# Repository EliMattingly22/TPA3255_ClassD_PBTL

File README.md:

# TPA3255_ClassD_PBTL
A KiCAD project for the TPA3255 amplifier in PBTL mode

This repository contains schematics, PCB layout and documentation for a compact, rack mountable PBTL (Parallel Bridged) Class‑D amplifier based on the Texas Instruments TPA3255. The design is intended to house three amplifier modules in a single 2U rack enclosure and includes front‑panel controls such as button‑enabled DC‑coupling, balanced XLR inputs/outputs, and protection/status indicators.

## Features

- TPA3255 Class‑D amplifier modules configured in PBTL(parallel bridge-tied load) mode
- Per‑channel button to toggle DC‑coupling
- Balanced XLR inputs
- Per‑channel protection: overcurrent, overtemperature, 
- Clipping indicators
- Per‑channel status LEDs (PWR GOOD / CLIP / FAULT)
- Mechanical layout and enclosure guidance for three amplifiers in a 2U rack unit

## Key electrical parameters

- Supply voltage - 24-52V
  - Power supply current rating should be sufficient for your load. At 50V a 12A supply will be enough for any application, but less is suitable for many other applications. 
- Gain is fixed. G = 21.6(2 Ohms) to 24.4(15 Ohms)
- THD depends on amplitude/power but generally 0.1-0.5%. Better than that in some operating conditions/power levels. 
- Output noise (1-25kHz) is approximately 2 microVolts/sqrt(Hz) 
- Quiescent power draw - about 100 mA per channel

## Overview

This project is intended as a general-purpose amplifier capable of replacing the AE Techron 7224 in a variety of lower-power applications. It is a high‑efficiency, medium‑power (300 Watt for sure and up to 600W, in theory...) amplifier solution with balanced I/O and configurable output coupling. The DC‑coupling button lets users switch the amplifier output between AC coupling and DC coupling for use with audio systems or laboratory instruments, etc. that require true DC‑coupled operation. The enclosure is designed to hold three amplifier modules in a 19" 2U rack, with appropriate heatsinking and airflow considerations.

### In this repository:

 - The enclosure is in the top level as: "TPA3255PBTL_Enclosure.step" [Here](TPA3255PBTL_Enclosure.step)
 - There is an add-on board in the directory "Current Control Board" Which allows the user to configure it as a current-mode amplifier with an external current sensor (ACS711)

## Important Design Notes

- Balanced XLR pinout: Pin 1 = GND, Pin 2 = Hot (+), Pin 3 = Cold (−).

- If you enable DC‑coupling, verify output DC offset is within safe limits for connected device. For a transformer, this may be problematic. 

- XLR output: It is not a high-power connector so if the application requires high-current, it would be a good idea to solder directly to the PCB and/or rework the board for a different connector.

## Possible configurations
I designed it for two distinct applications, stepping-DC waveforms (i.e. staircase like waves), and pure sine waves. As the requirements are quite different between the two, there is two output filter configurations. For the DC staircases, the filter uses ferrite cores. For the sine waves, the output filter uses air-core inductors to minimize the risk of adding distortions. 

## Mechanical & Enclosure Guidance (3 amps in 2U rack)

- Standard 19" width, 2U height (88.9 mm). 
- Depth = 145 mm not including XLR connectors, which should have about 100 mm of space for the cable/bend
- XLR inputs on front and rear panel
- Speaker outputs on rear

## BOM notes

- Heatsink hardware = Advanced Thermal Solutions Inc. ATS-TI1OP-519-C1-R3
- Inductor core (for DC version) = Magnetics, a division of Spang & Co., 0079894A7HT19
  - Coated Kool Mu MAX Ferrite Core Toroid Type Length Width 1.060" (26.92mm) Diameter 0.708" (17.99mm) Height
  - Wind with three parallel strands of 18AWG magnet wire, 11 turns 

## Filter inductors

### High power (Lower linearity)
Using ferrite cores improves the efficiency (less copper losses) at the expense of some harmonic distortion. The first-stage core, L2 and L3, must carry the ripple current from the switching. The switching frequency is about 500 kHz (2 uSec period), so if it is switching 50 V every 1 uSec, at periodic steady state when the average voltage across the inductor is 0 V and so each half-period has 25 V across the inductor, the ripple current will be 2.5 A (di/dt = V/L = 25 / 10 uH = 2.5 A/uSec). The original inductor Bourns Inc. 2101-V-RC did not tolerate this well and increased the quiescent current to about 200 mA per channel and induced considerable losses into the system at higher currents. To reduce the inductor losses, this was replaced with the 0079894A7HT19 with 11 turns of three strands of 18AWG magnet wire. This core was chosen for the high saturation magnetization and fairly low losses. The datasheet specifies that the 20% reduction in inductance will occur with 320 Amp-turns so just about 30 Amps, which is more than the amplifier can output anyway. 

### High linearity
Ferrite inductors are inherently nonlinear, so for the applications that require high purity waveforms, an air core inductor was wound and only a single stage of output filtering. The inductor former (rectangular cylinder) is 22mm tall, 35mm OD, 12mm ID, and has 38 turns of 18 AWG magnet wire (about 3.3 m of wire with some extra to be cut off). The inductance was 10 uH and 200 mOhms at 50kHz. Litz wire would reduce the losses somewhat, but I wanted to avoid using Litz for this project. 

## Filter capacitors

The original capacitors (B32529D1105J289) are fine for low-frequency applications, but for >10 kHz, they should be replaced with ones which can tolerate the current being driven into them by the amplifier. At 25 kHz, the reactance is only 6.4 Ohms, so at 50 V there would be nearly 10 A of current flowing into the capacitors. I suggest much larger, much lower loss polypropylene film capacitors (e.g. R76 series or similar, and at least 300VAC rating). They will either need to be bodged onto the board (like I did) or rework the PCB to accomodate it. 

# Measurements

## Output power

### 2.5 Ohm load

After about 3 minutes with a 51V supply, 6 Amps being drawn (306W), the amplifier overheated. It reset via the front-panel button after cooling off.Note: there wasnt much forced air over the fins.

### 5 Ohm load
With 47 Vpk (1 kHz) into 5 Ohm load, the system reached a steady state.
- Heat sink: 67 C
- Small output inductors: 77 C

### 7.7 Ohm load
With 45.8 Vpk (1 kHz) into 7.7 Ohm load, the system reached a steady state.

## Gain

### Air core inductor output filter

### Ferrite core inductor output filter

### Low Freq characteristics, effect of jumpers on input

## THD
All measurements with the wide BW/DC enabled mode. Measured the voltage across the load with a RP1025D differential probe 20x range. The probe itself has about 0.1-0.5% THD at 1kHz. 
### Ferrite output filter, 15 Ohm load:

### Air core inductor filter, 15 Ohm load:

### Air core inductor filter, 2 Ohm load:

## Noise, input terminated, 2 Ohm load

## Safety & Compliance Notes

- DC‑coupled outputs can damage speakers/transformers/other loads if misused 
- For commercial use verify thermal/electrical safety per applicable standards (IEC/UL) and plan for certification where required.

# Schematic details:

The output filter sheet shows the post-switching LC network and probe connectors used to tame the 500 kHz ripple. It is important to keep the filter inductor above 5 uH, per the datasheet. C18/19 present low impedance at high frequencies mitigating some RF noise when the ESL of the larger capacitors would limit their effectiveness. C20/R8 stabilize the impedance at higher frequencies. 

The Second stage filter, L4/C8/C36 and its opposite pair can be included or not depending on the application. They will be a bit lossy but add additional filtering stages to mitigate higher frequency noise. These are not populated in the air core filter version becasuse that application has another filter external to this amplifier board. 

The LED page documents the front-panel status indicators, including the current-limit, clip, and fault drivers tied into the protection logic. See the datasheet for details on the logic. 

The power sheet covers the main supply routing, bulk capacitance, and bias regulation stages that feed the TPA3255 module and housekeeping rails.

Note that there is a reverse voltage protection PMOS, the Zener diode protects it from too high VGS.

There are also LEDs to indicate each of the four rails are working (well that there is power to them, they may be enabled but the rails be incorrect). 

The signals schematic captures the balanced input conditioning, relay-controlled coupling paths, etc.

The signal either passes throught the AC coupling capacitors, C15/43 (the values of which should be chosen based on the application), and are bypassed in DC coupled mode by the latching switch. It then goes through a Diff->SE stage (U4A) which sets the reference point to be 3.8V. The signal then is buffered and turned into a differential signal either going through large AC coupling caps or through jumpers J4/5 which need to be shorted for true DC coupling mode. 

RV1 allows offset trimming.

U7A/B allows for external voltage monitoring, via a home-brew high signal instrumentation amplifier setup, if needed. There is only a test point, but a wire could be easily soldered and a connector added if desired. 

The startup page highlights inrush limiting, sequencing, and reset circuitry that ensures the amplifier powers up quietly without tripping protection as suggested by the datasheet. Initially the capacitor holds Q4 low, which means Q5 is enabled, pulling the RST to gnd, but when the capacitor charges, Q4 conducts pulling the gate of Q5 down and R52 pulls RST high.

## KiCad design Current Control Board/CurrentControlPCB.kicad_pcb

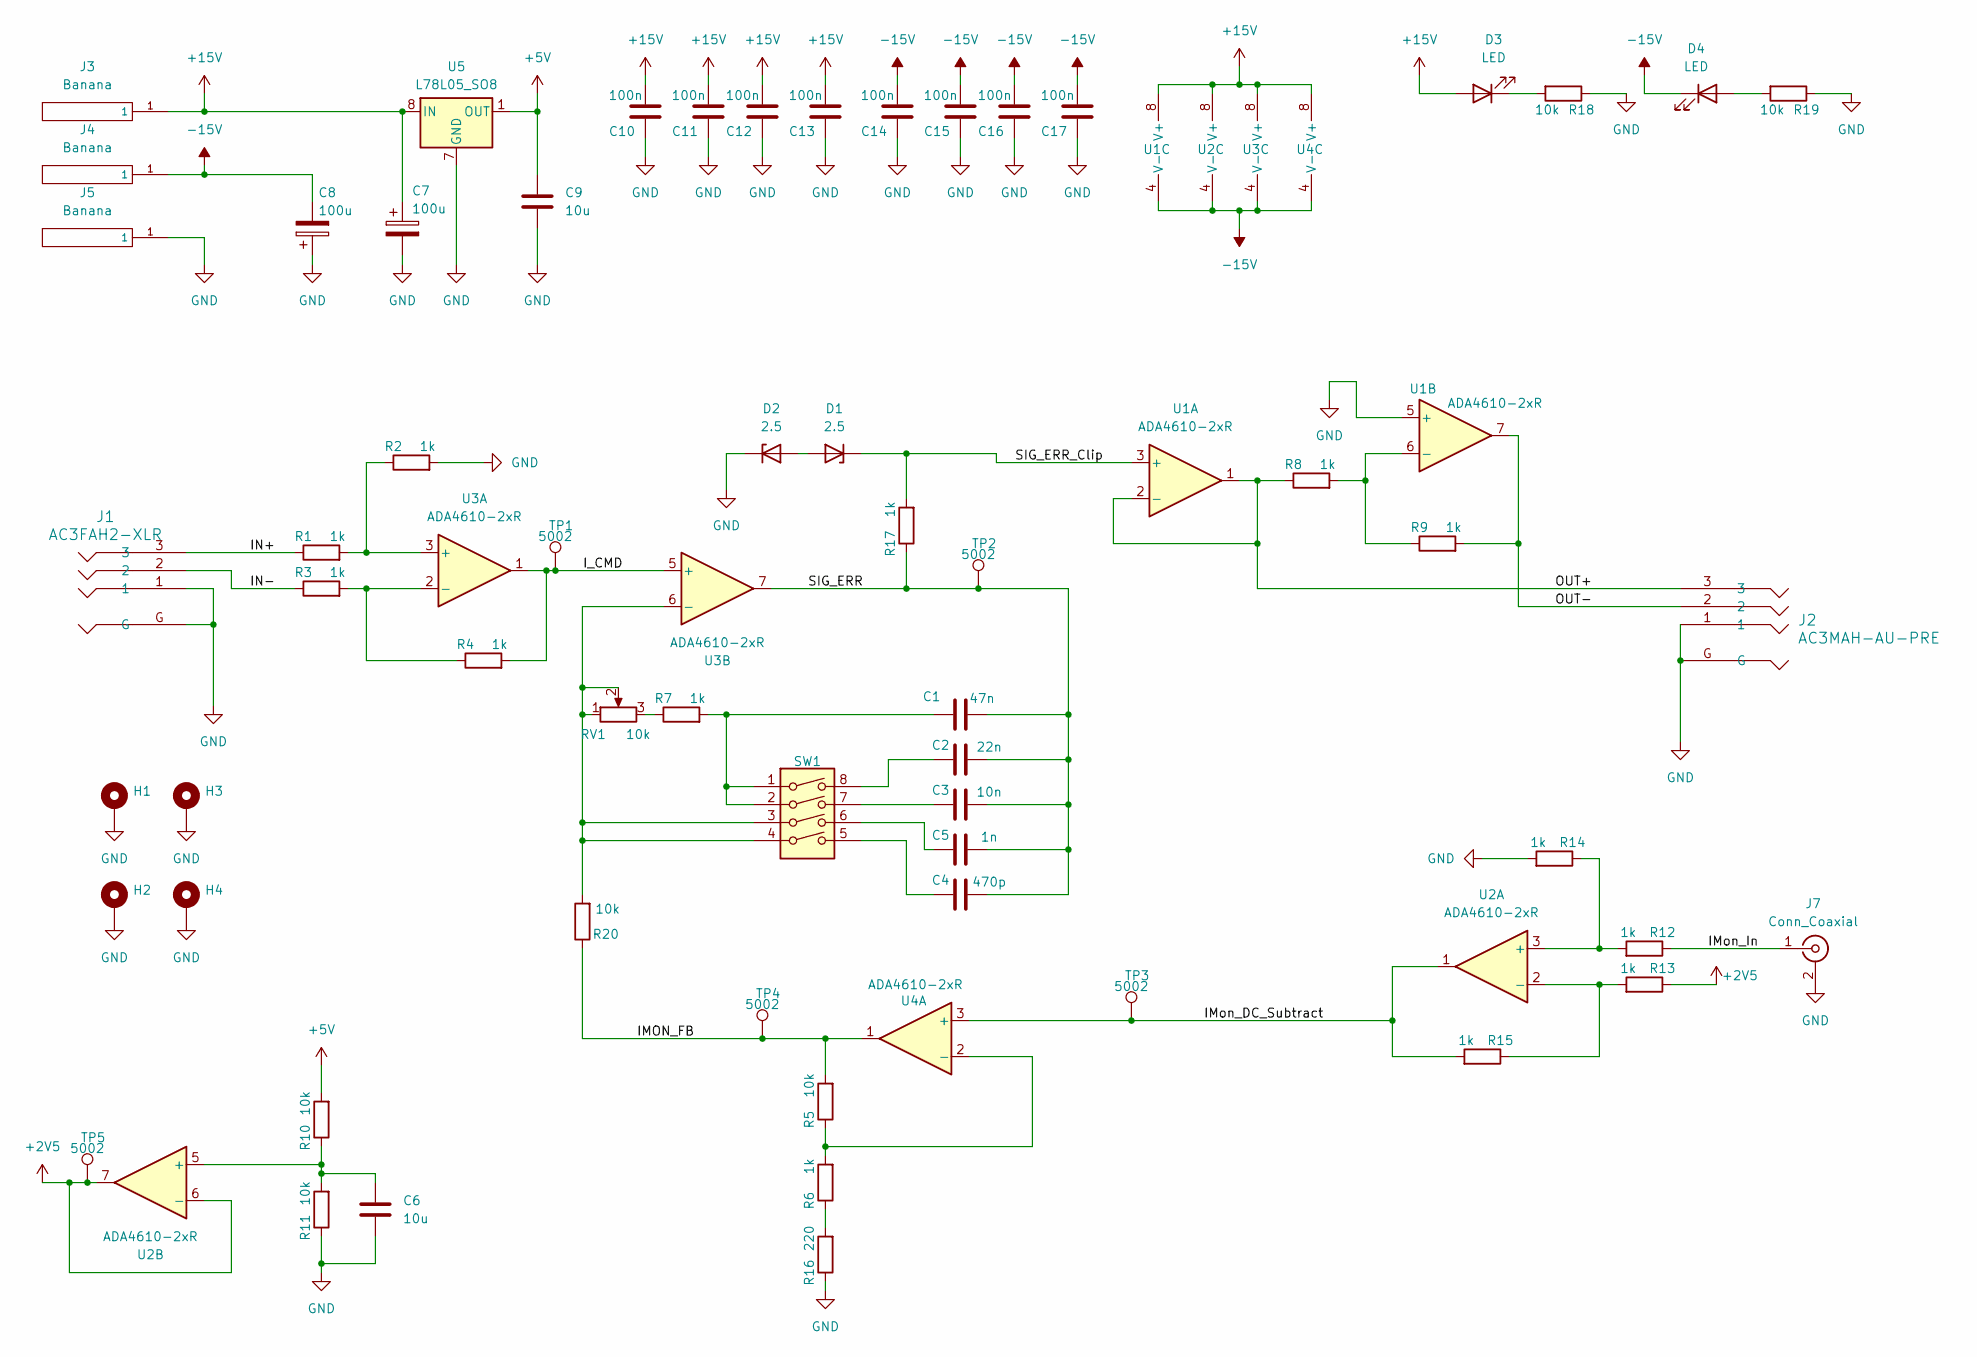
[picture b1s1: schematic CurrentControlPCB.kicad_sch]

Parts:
C1: 47n; C_0805_2012Metric_Pad1.18x1.45mm_HandSolder
C2: 22n; C_0805_2012Metric_Pad1.18x1.45mm_HandSolder
C3: 10n; C_0805_2012Metric_Pad1.18x1.45mm_HandSolder
C4: 470p; C_0805_2012Metric_Pad1.18x1.45mm_HandSolder
C5: 1n; C_0805_2012Metric_Pad1.18x1.45mm_HandSolder
C6, C9: 10u; C_0805_2012Metric_Pad1.18x1.45mm_HandSolder
C7, C8: 100u; CP_Radial_D6.3mm_P2.50mm
C10, C11, C12, C13, C14, C15, C16, C17: 100n; C_0805_2012Metric_Pad1.18x1.45mm_HandSolder
D1, D2: 2.5; D_SOD-123
D3, D4: LED; LED_0805_2012Metric_Pad1.15x1.40mm_HandSolder
H1, H2, H3, H4: MountingHole_3.2mm_M3_DIN965_Pad
J1: AC3FAH2-XLR; AC3FAH2-F-XLR
J2: AC3MAH-AU-PRE; AC3MAH-AU-PRE_AMP
J3, J4, J5: Banana; Banana-FCR7350L
J7: Conn_Coaxial; 31-5486-1010 BNC Panel RA
R1, R2, R3, R4, R6, R7, R8, R9, R12, R13, R14, R15, R17: 1k; R_0805_2012Metric_Pad1.20x1.40mm_HandSolder
R5, R10, R11, R18, R19, R20: 10k; R_0805_2012Metric_Pad1.20x1.40mm_HandSolder
R16: 220; R_0805_2012Metric_Pad1.20x1.40mm_HandSolder
RV1: 10k; Potentiometer_Bourns_3296W_Vertical
SW1: SW_DIP_x04; SW_DIP_SPSTx04_Slide_9.78x12.34mm_W8.61mm_P2.54mm
TP1, TP2, TP3, TP4, TP5: 5002; TestPoint_Loop_D2.50mm_Drill1.0mm
U1, U2, U3, U4: ADA4610-2xR; SOIC-8_3.9x4.9mm_P1.27mm
U5: L78L05_SO8; SOIC-8_3.9x4.9mm_P1.27mm

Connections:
+2V5: R13.1, TP5.1, U2.6 (-), U2.7
+5V: C9.2, R10.2, U5.1 (OUT)
+15V: C7.1, C10.2, C11.2, C12.2, C13.2, D3.2 (A), J3.1, U1.8 (V+), U2.8 (V+), U3.8 (V+), U4.8 (V+), U5.8 (IN)
-15V: C8.2, C14.2, C15.2, C16.2, C17.2, D4.1 (K), J4.1, U1.4 (V-), U2.4 (V-), U3.4 (V-), U4.4 (V-)
/IMON_FB: R5.2, R20.1, TP4.1, U4.1
/IMon_DC_Subtract: R15.2, TP3.1, U2.1, U4.3 (+)
/IMon_In: J7.1 (In), R12.1
/IN+: J1.3, R1.1
/IN-: J1.2, R3.1
/I_CMD: R4.2, TP1.1, U3.1, U3.5 (+)
/OUT+: J2.3, R8.1, U1.1, U1.2 (-)
/OUT-: J2.2, R9.2, U1.7
/SIG_ERR: C1.2, C2.2, C3.2, C4.2, C5.2, R17.1, TP2.1, U3.7
/SIG_ERR_Clip: D1.1 (K), R17.2, U1.3 (+)
GND: C6.1, C7.2, C8.1, C9.1, C10.1, C11.1, C12.1, C13.1, C14.1, C15.1, C16.1, C17.1, D2.1 (K), H1.1, H2.1, H3.1, H4.1, J1.1, J1.G, J2.1, J2.G, J5.1, J7.2 (Ext), R2.2, R11.1, R14.2, R16.1, R18.1, R19.1, U1.5 (+), U5.2 (GND), U5.3 (GND), U5.6 (GND), U5.7 (GND)
unnamed: C1.1, R7.2, SW1.1, SW1.2
unnamed: C2.1, SW1.8
unnamed: C3.1, SW1.7
unnamed: C4.1, SW1.5
unnamed: C5.1, SW1.6
unnamed: D1.2 (A), D2.2 (A)
unnamed: D3.1 (K), R18.2
unnamed: D4.2 (A), R19.2
unnamed: R7.1, RV1.3
unnamed: R6.1, R16.2
unnamed: R8.2, R9.1, U1.6 (-)
unnamed: R12.2, R14.1, U2.3 (+)
unnamed: R13.2, R15.1, U2.2 (-)
unnamed: C6.2, R10.1, R11.2, U2.5 (+)
unnamed: R1.2, R2.1, U3.3 (+)
unnamed: R3.2, R4.1, U3.2 (-)
unnamed: R20.2, RV1.1, RV1.2, SW1.3, SW1.4, U3.6 (-)
unnamed: R5.1, R6.2, U4.2 (-)

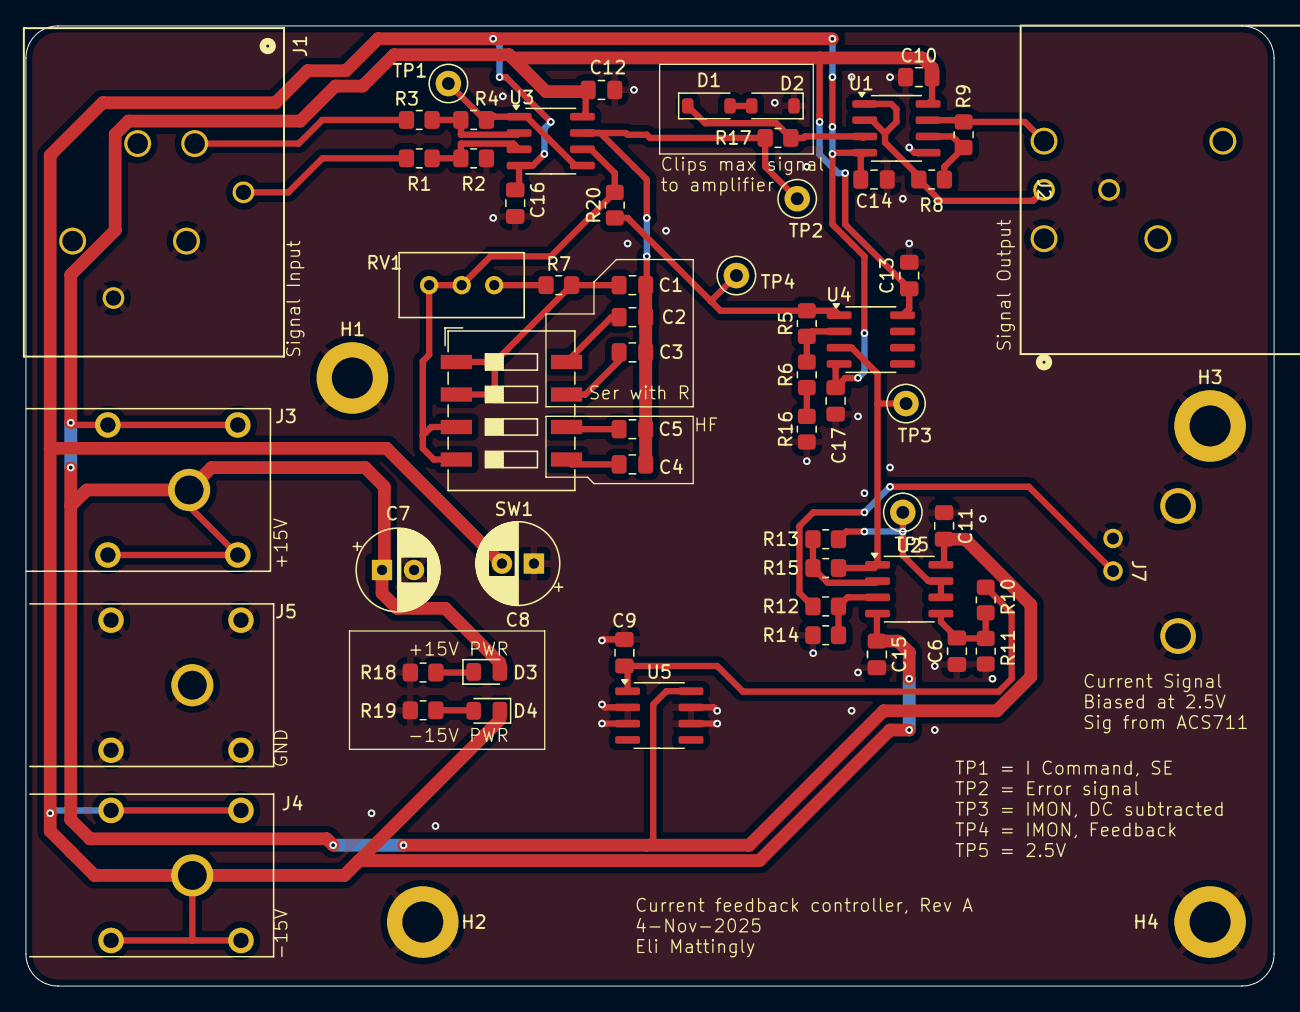
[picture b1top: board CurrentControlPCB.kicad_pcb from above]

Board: 2 copper layers, 97.5 x 75.0 mm, 63 parts (0 on the bottom side), 33 nets.

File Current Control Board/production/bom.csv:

Designator,Footprint,Quantity,Value,LCSC Part #
C1,0805,1,47n,
"C10, C11, C12, C13, C14, C15, C16, C17",0805,8,100n,
C2,0805,1,22n,
C3,0805,1,10n,
C4,0805,1,470p,
C5,0805,1,1n,
"C6, C9",0805,2,10u,
"C7, C8",CP_Radial_D6.3mm_P2.50mm,2,100u,
"D1, D2",D_SOD-123,2,2.5,
"D3, D4",0805,2,LED,
J1,AC3FAH2-F-XLR,1,AC3FAH2-XLR,
J2,AC3MAH-AU-PRE_AMP,1,AC3MAH-AU-PRE,
"J3, J4, J5",Banana-FCR7350L,3,Banana,
J7,31-5486-1010 BNC Panel RA,1,Conn_Coaxial,
"R1, R12, R13, R14, R15, R17, R2, R3, R4, R6, R7, R8, R9",0805,13,1k,
"R10, R11, R18, R19, R20, R5",0805,6,10k,
R16,0805,1,220,
RV1,Potentiometer_Bourns_3296W_Vertical,1,10k,
SW1,SW_DIP_SPSTx04_Slide_9.78x12.34mm_W8.61mm_P2.54mm,1,SW_DIP_x04,
"TP1, TP2, TP3, TP4, TP5",TestPoint_Loop_D2.50mm_Drill1.0mm,5,5002,
"U1, U2, U3, U4",SOIC-8_3.9x4.9mm_P1.27mm,4,ADA4610-2xR,
U5,SOIC-8_3.9x4.9mm_P1.27mm,1,L78L05_SO8,

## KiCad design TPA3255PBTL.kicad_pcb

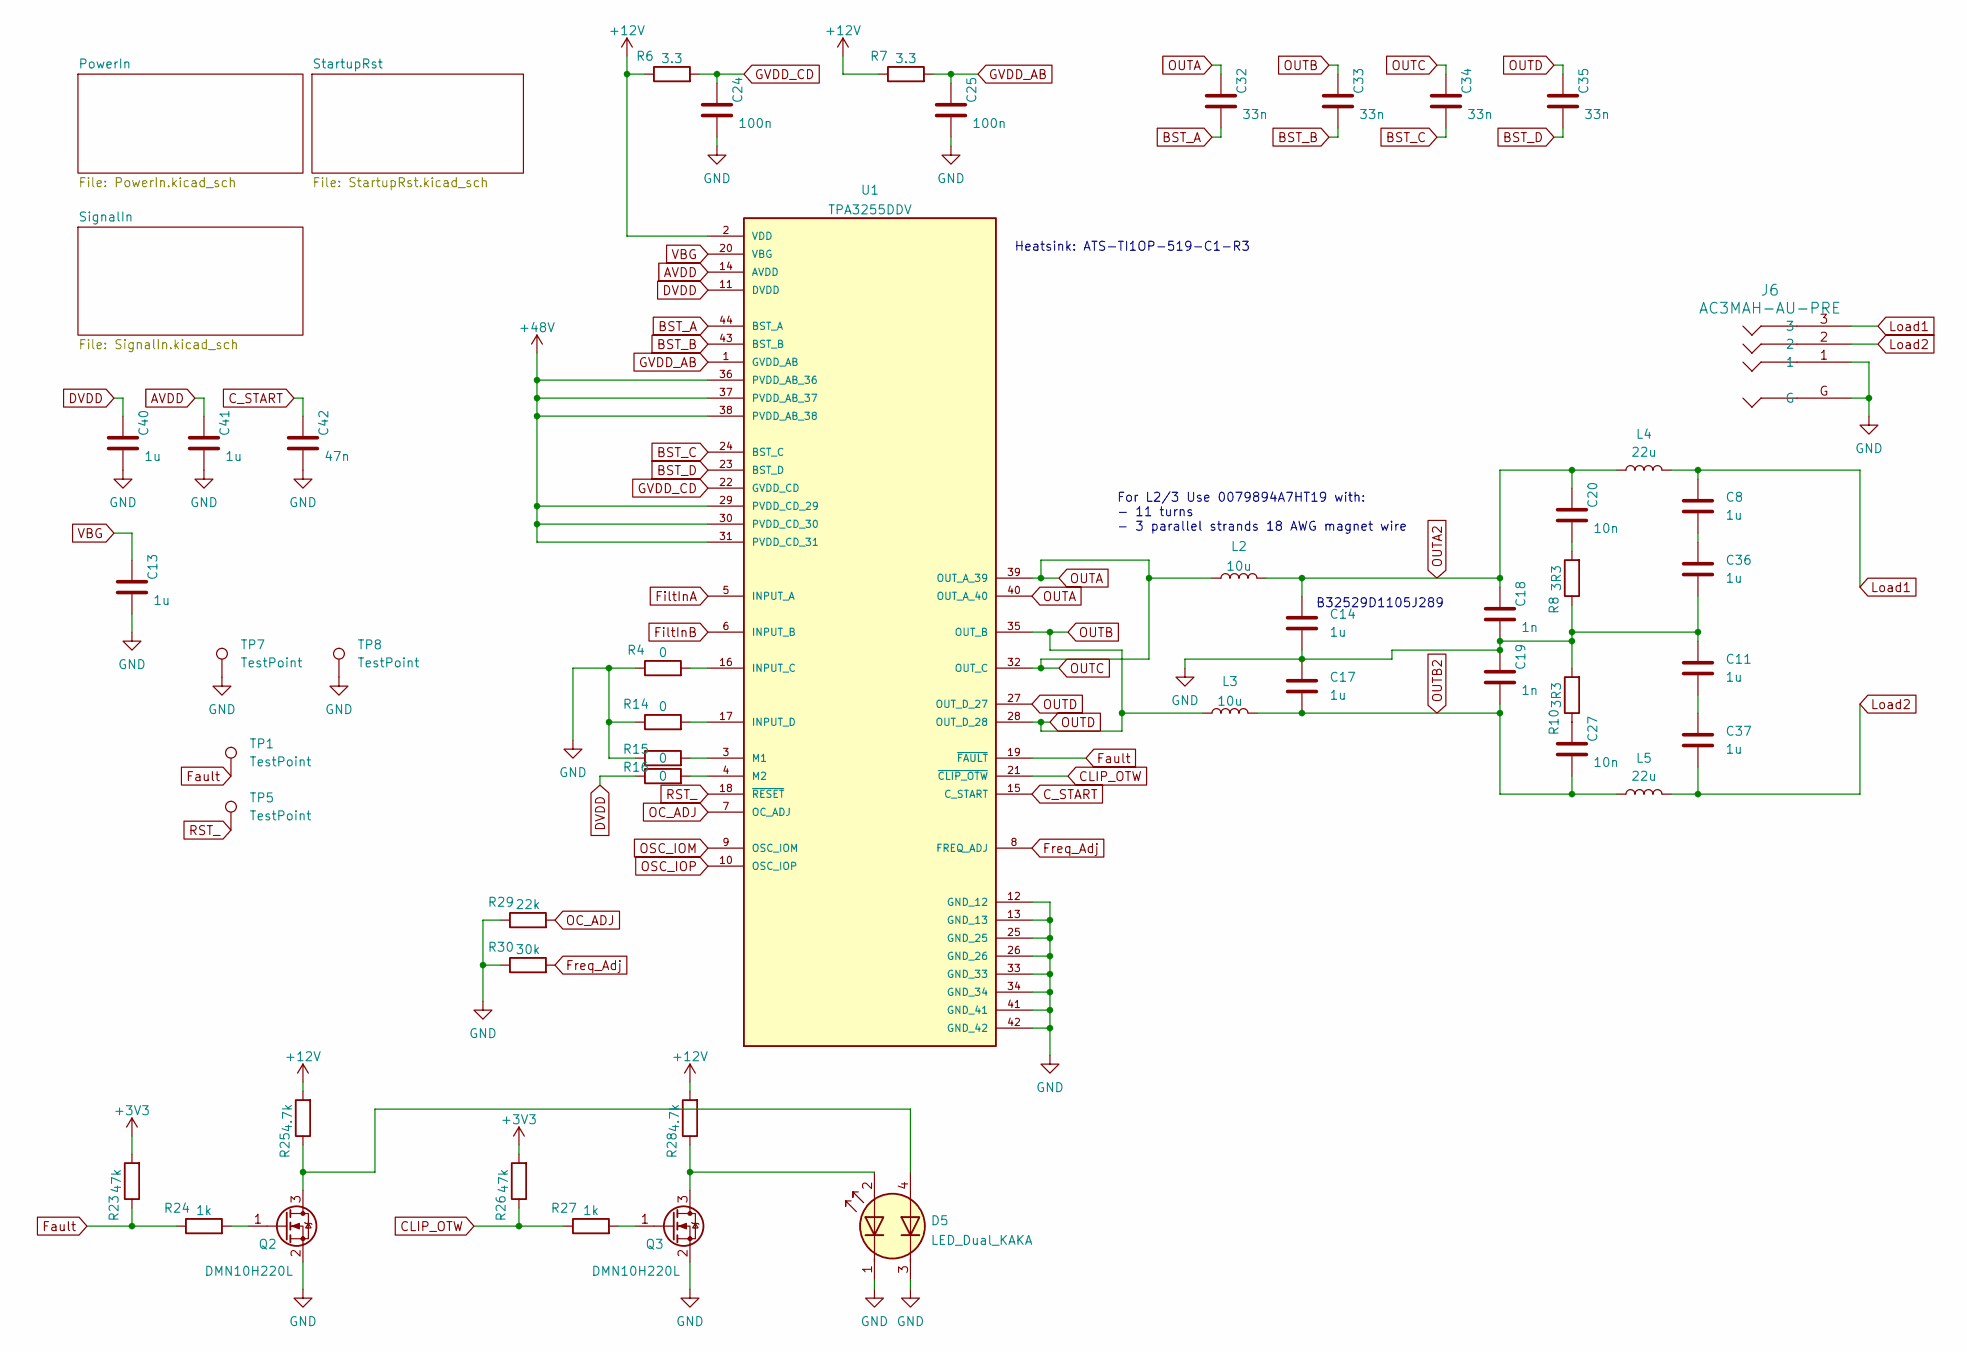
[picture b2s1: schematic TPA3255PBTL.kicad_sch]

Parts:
C8, C11, C14, C17, C36, C37: 1u; C_Rect_L7.2mm_W7.2mm_P5.00mm_FKS2_FKP2_MKS2_MKP2
C13, C40, C41: 1u; C_0805_2012Metric
C18, C19: 1n; C_0805_2012Metric
C20, C27: 10n; C_0805_2012Metric
C24, C25: 100n; C_0805_2012Metric
C32, C33, C34, C35: 33n; C_0805_2012Metric
C42: 47n; C_0805_2012Metric
D5: LED_Dual_KAKA; IC4_WP934EB_2GD_KNB
J6: AC3MAH-AU-PRE; AC3MAH-AU-PRE_AMP
L2, L3: 10u; L_Toroid_Vertical_L22.4mm_W10.2mm_P7.90mm_Vishay_TJ4
L4, L5: 22u; L_Toroid_Vertical_L22.4mm_W10.2mm_P7.90mm_Vishay_TJ4
Q2, Q3: DMN10H220L; SOT-23
R4, R14, R15, R16: 0; R_0805_2012Metric
R6, R7: 3.3; R_0805_2012Metric
R8, R10: 3R3; R_0805_2012Metric
R23, R26: 47k; R_0805_2012Metric
R24, R27: 1k; R_0805_2012Metric
R25, R28: 4.7k; R_0805_2012Metric
R29: 22k; R_0805_2012Metric
R30: 30k; R_0805_2012Metric
TP1, TP5, TP7, TP8: TestPoint; TestPoint_THTPad_1.0x1.0mm_Drill0.5mm
U1: TPA3255DDV; SOP63P810X120-44N; PARTREV A

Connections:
+3V3: R23.2, R26.2; also elsewhere on the board
+12V: R6.1, R7.1, R25.2, R28.2, U1.2 (VDD); also elsewhere on the board
+48V: U1.29 (PVDD_CD_29), U1.30 (PVDD_CD_30), U1.31 (PVDD_CD_31), U1.36 (PVDD_AB_36), U1.37 (PVDD_AB_37), U1.38 (PVDD_AB_38); also elsewhere on the board
AVDD: C41.1, U1.14 (AVDD)
BST_A: C32.2, U1.44 (BST_A)
BST_B: C33.2, U1.43 (BST_B)
BST_C: C34.2, U1.24 (BST_C)
BST_D: C35.2, U1.23 (BST_D)
CLIP_OTW: R26.1, R27.1, U1.21 (~CLIP_OTW)
C_START: C42.1, U1.15 (C_START)
DVDD: C40.1, R16.1, U1.11 (DVDD)
Fault: R23.1, R24.1, TP1.1, U1.19 (~FAULT)
FiltInA: U1.5 (INPUT_A); also elsewhere on the board
FiltInB: U1.6 (INPUT_B); also elsewhere on the board
Freq_Adj: R30.2, U1.8 (FREQ_ADJ)
GND: C11.1, C13.2, C14.2, C17.1, C18.2, C19.1, C24.2, C25.2, C36.2, C40.2, C41.2, C42.2, D5.1 (A1), D5.3 (A2), J6.1, J6.G, Q2.2 (S), Q3.2 (S), R4.1, R8.1, R10.2, R14.1, R15.1, R29.1, R30.1, TP7.1, TP8.1, U1.12 (GND_12), U1.13 (GND_13), U1.25 (GND_25), U1.26 (GND_26), U1.33 (GND_33), U1.34 (GND_34), U1.41 (GND_41), U1.42 (GND_42); also elsewhere on the board
GVDD_AB: C25.1, R7.2, U1.1 (GVDD_AB)
GVDD_CD: C24.1, R6.2, U1.22 (GVDD_CD)
Load1: C8.1, J6.3, L4.2; also elsewhere on the board
Load2: C37.2, J6.2, L5.2; also elsewhere on the board
unnamed: C11.2, C37.1
unnamed: C20.2, R8.2
unnamed: C27.1, R10.1
unnamed: C8.2, C36.1
unnamed: D5.2 (K1), Q3.3 (D), R28.1
unnamed: D5.4 (K2), Q2.3 (D), R25.1
unnamed: Q2.1 (G), R24.2
unnamed: Q3.1 (G), R27.2
unnamed: R4.2, U1.16 (INPUT_C)
unnamed: R14.2, U1.17 (INPUT_D)
unnamed: R15.2, U1.3 (M1)
unnamed: R16.2, U1.4 (M2)
OC_ADJ: R29.2, U1.7 (OC_ADJ)
OSC_IOM: U1.9 (OSC_IOM)
OSC_IOP: U1.10 (OSC_IOP)
OUTA: C32.1, C34.1, L2.1, U1.32 (OUT_C), U1.39 (OUT_A_39), U1.40 (OUT_A_40)
OUTA2: C14.1, C18.1, C20.1, L2.2, L4.1
OUTB: C33.1, C35.1, L3.1, U1.27 (OUT_D_27), U1.28 (OUT_D_28), U1.35 (OUT_B)
OUTB2: C17.2, C19.2, C27.2, L3.2, L5.1
RST_: TP5.1, U1.18 (~RESET); also elsewhere on the board
VBG: C13.1, U1.20 (VBG)

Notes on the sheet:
B32529D1105J289
For L2/3 Use 0079894A7HT19 with: - 11 turns - 3 parallel strands 18 AWG magnet wire
Heatsink: ATS-TI1OP-519-C1-R3

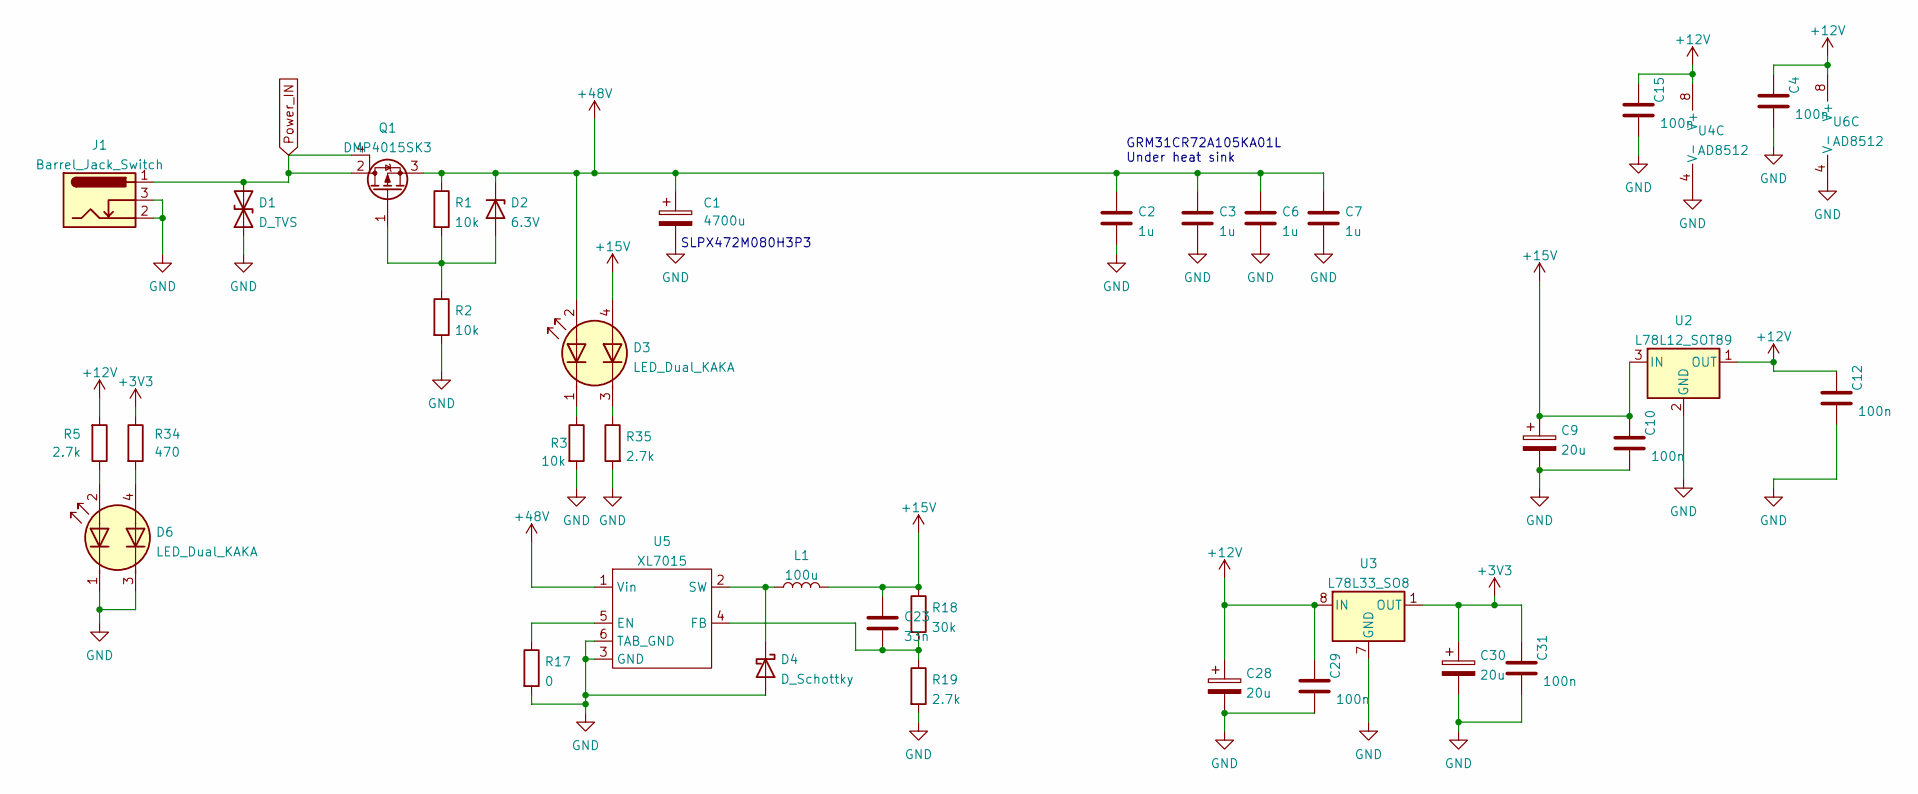
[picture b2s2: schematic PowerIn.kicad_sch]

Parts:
C1: 4700u; CP_Radial_D35.0mm_P10.00mm_SnapIn
C2, C3, C6, C7: 1u; C_1206_3216Metric
C4, C10, C12, C15, C29, C31: 100n; C_0805_2012Metric
C9, C28, C30: 20u; CP_Radial_D6.3mm_P2.50mm
C23: 33n; C_0805_2012Metric
D1: D_TVS; D_SOD-123
D2: 6.3V; D_SOD-123
D3, D6: LED_Dual_KAKA; IC4_WP934EB_2GD_KNB
D4: D_Schottky; D_SOD-123
J1: Barrel_Jack_Switch; BarrelJack_GCT_DCJ200-10-A_Horizontal
L1: 100u; MWPY8040; LCSC C501759
Q1: DMP4015SK3; TO-252-3_TabPin4
R1, R2, R3: 10k; R_0805_2012Metric
R5, R19, R35: 2.7k; R_0805_2012Metric
R17: 0; R_0805_2012Metric
R18: 30k; R_0805_2012Metric
R34: 470; R_0805_2012Metric
U2: L78L12_SOT89; SOT-89-3
U3: L78L33_SO8; SOIC-8_3.9x4.9mm_P1.27mm
U4, U6: AD8512; SO-8_3.9x4.9mm_P1.27mm
U5: XL7015; XL7015E1

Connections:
+3V3: C30.1, C31.1, R34.1, U3.1 (OUT); also elsewhere on the board
+12V: C4.1, C12.1, C15.1, C28.1, C29.1, R5.2, U2.1 (OUT), U3.8 (IN), U4.8 (V+), U6.8 (V+); also elsewhere on the board
+15V: C9.1, C10.1, C23.1, D3.4 (K2), L1.2, R18.1, U2.3 (IN)
+48V: C1.1, C2.1, C3.1, C6.1, C7.1, D2.1 (K), D3.2 (K1), Q1.3 (S), R1.1, U5.1 (Vin); also elsewhere on the board
GND: C1.2, C2.2, C3.2, C4.2, C6.2, C7.2, C9.2, C10.2, C12.2, C15.2, C28.2, C29.2, C30.2, C31.2, D1.1 (A1), D4.2 (A), D6.1 (A1), D6.3 (A2), J1.2, J1.3, R2.2, R3.2, R17.2, R19.2, R35.2, U2.2 (GND), U3.2 (GND), U3.3 (GND), U3.6 (GND), U3.7 (GND), U4.4 (V-), U5.3 (GND), U5.6 (TAB_GND), U6.4 (V-); also elsewhere on the board
unnamed: D2.2 (A), Q1.1 (G), R1.2, R2.1
unnamed: D3.1 (A1), R3.1
unnamed: D3.3 (A2), R35.1
unnamed: D4.1 (K), L1.1, U5.2 (SW)
unnamed: D6.2 (K1), R5.1
unnamed: D6.4 (K2), R34.2
unnamed: R17.1, U5.5 (EN)
unnamed: C23.2, R18.2, R19.1, U5.4 (FB)
Power_IN: D1.2 (A2), J1.1, Q1.2 (D), Q1.4 (D)

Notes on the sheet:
GRM31CR72A105KA01L Under heat sink
SLPX472M080H3P3

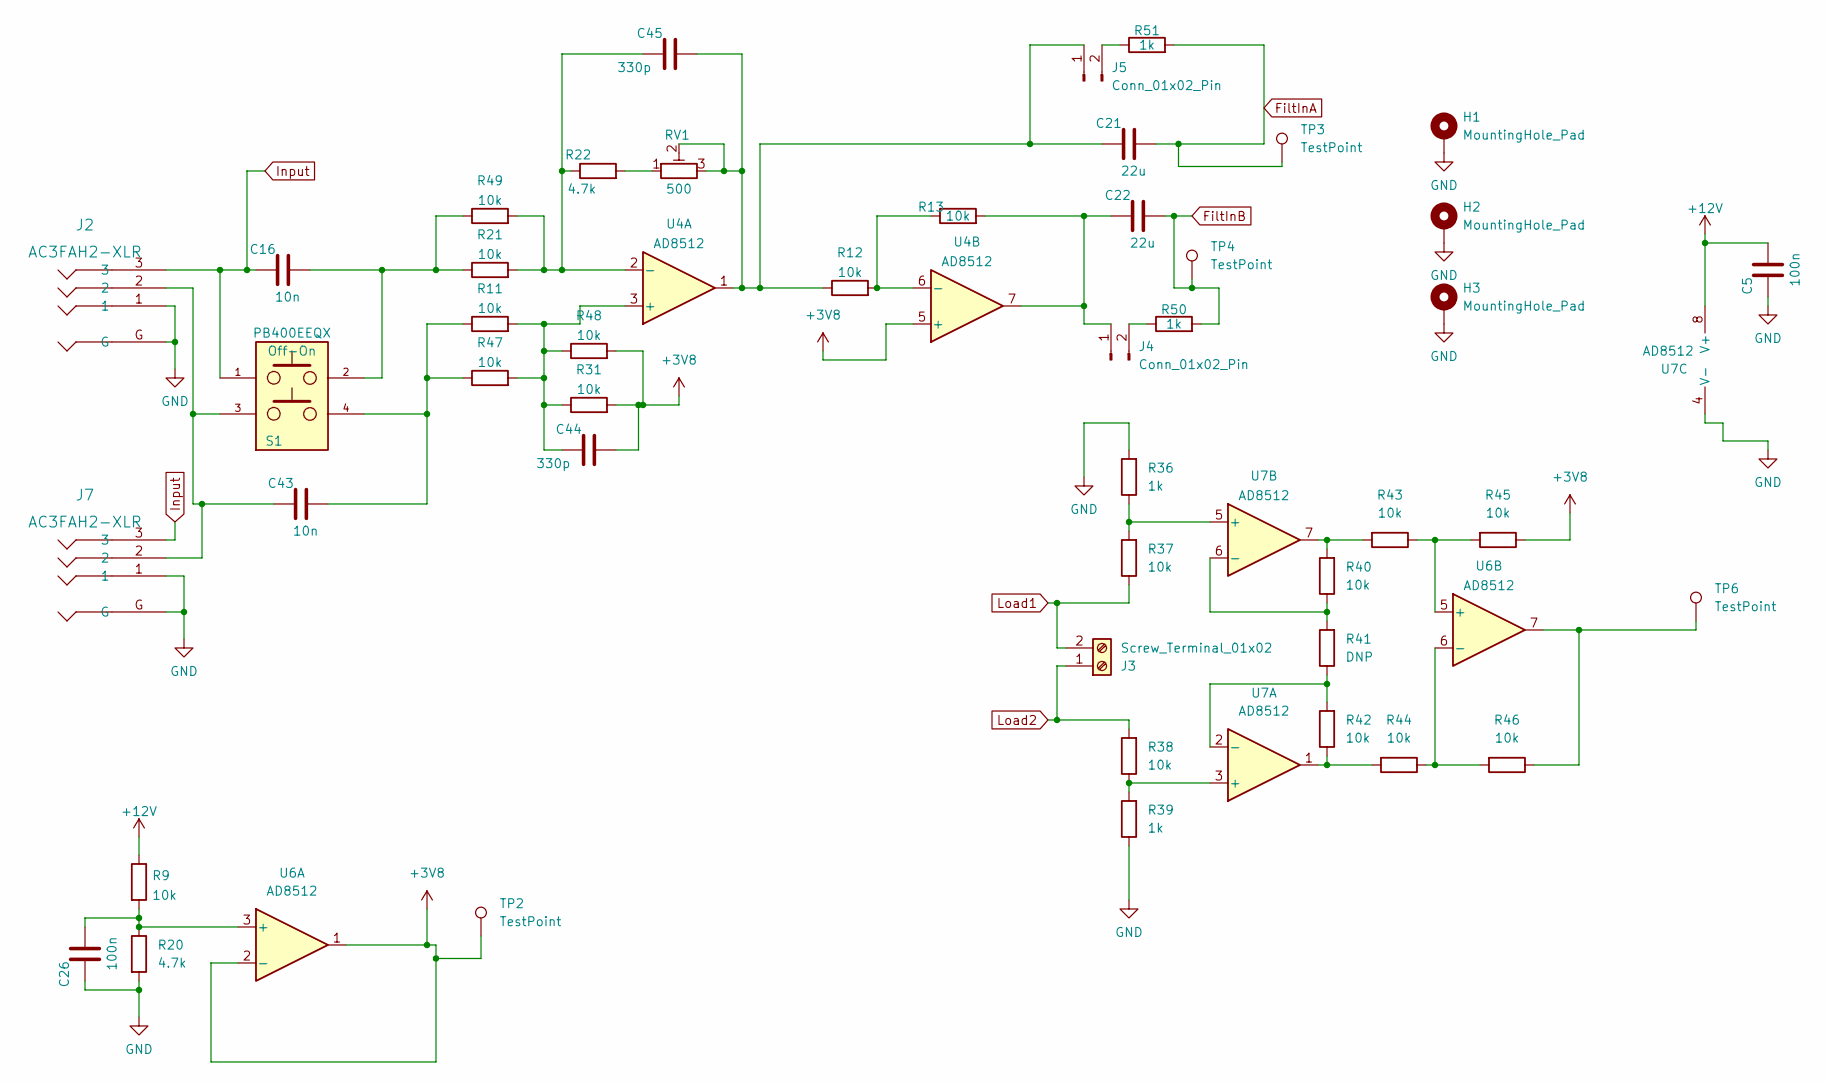
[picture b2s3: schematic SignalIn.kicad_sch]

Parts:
C5, C26: 100n; C_0805_2012Metric
C16, C43: 10n; C_0805_2012Metric
C21, C22: 22u; C_1206_3216Metric_Pad1.33x1.80mm_HandSolder
C44, C45: 330p; C_0805_2012Metric
H1, H2, H3: MountingHole_Pad; MountingHole_3.2mm_M3_Pad_Via
J2, J7: AC3FAH2-XLR; AC3FAH2-F-XLR
J3: Screw_Terminal_01x02; TerminalBlock_Phoenix_MKDS-1,5-2-5.08_1x02_P5.08mm_Horizont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
J4, J5: Conn_01x02_Pin; PinHeader_1x02_P1.27mm_Vertical
R9, R11, R12, R13, R21, R31, R37, R38, R40, R42, R43, R44, R45, R46, R47, R48, R49: 10k; R_0805_2012Metric
R20, R22: 4.7k; R_0805_2012Metric
R36, R39, R50, R51: 1k; R_0805_2012Metric
R41: DNP; R_0805_2012Metric
RV1: 500; Potentiometer_Bourns_3296W_Vertical
S1: PB400EEQX; SW_PB400EEQX; PARTREV NA
TP2, TP3, TP4, TP6: TestPoint; TestPoint_THTPad_1.0x1.0mm_Drill0.5mm
U4, U6, U7: AD8512; SO-8_3.9x4.9mm_P1.27mm

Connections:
+3V8: C44.2, R31.2, R45.1, R48.2, TP2.1, U4.5 (+), U6.1, U6.2 (-)
+12V: C5.2, R9.1, U7.8 (V+); also elsewhere on the board
FiltInA: C21.2, R51.2, TP3.1; also elsewhere on the board
FiltInB: C22.2, R50.2, TP4.1; also elsewhere on the board
GND: C5.1, C26.1, H1.1, H2.1, H3.1, J2.1, J2.G, J7.1, J7.G, R20.2, R36.2, R39.1, U7.4 (V-); also elsewhere on the board
Input: C16.1, J2.3, J7.3, S1.1
Load1: J3.2, R37.1; also elsewhere on the board
Load2: J3.1, R38.2; also elsewhere on the board
unnamed: C16.2, R21.1, R49.1, S1.2
unnamed: C43.1, J2.2, J7.2, S1.3
unnamed: C43.2, R11.1, R47.1, S1.4
unnamed: C22.1, J4.1, R13.2, U4.7
unnamed: J4.2, R50.1
unnamed: C21.1, C45.2, J5.1, R12.1, RV1.2, RV1.3, U4.1
unnamed: J5.2, R51.1
unnamed: R22.2, RV1.1
unnamed: R40.2, R43.2, U7.7
unnamed: R42.1, R44.2, U7.1
unnamed: R46.1, TP6.1, U6.7
unnamed: C44.1, R11.2, R31.1, R47.2, R48.1, U4.3 (+)
unnamed: C45.1, R21.2, R22.1, R49.2, U4.2 (-)
unnamed: R12.2, R13.1, U4.6 (-)
unnamed: C26.2, R9.2, R20.1, U6.3 (+)
unnamed: R43.1, R45.2, U6.5 (+)
unnamed: R44.1, R46.2, U6.6 (-)
unnamed: R38.1, R39.2, U7.3 (+)
unnamed: R41.1, R42.2, U7.2 (-)
unnamed: R36.1, R37.2, U7.5 (+)
unnamed: R40.1, R41.2, U7.6 (-)

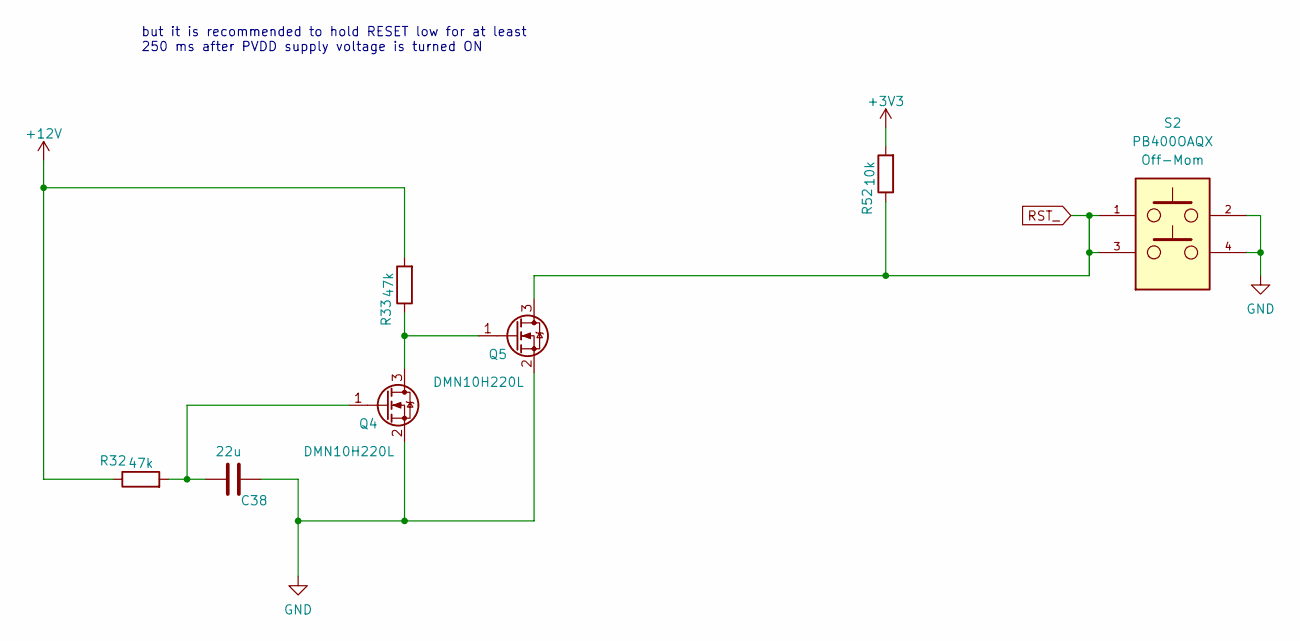
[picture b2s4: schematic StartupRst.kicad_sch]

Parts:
C38: 22u; C_1206_3216Metric_Pad1.33x1.80mm_HandSolder
Q4, Q5: DMN10H220L; SOT-23
R32, R33: 47k; R_0805_2012Metric
R52: 10k; R_0805_2012Metric
S2: PB400OAQX; SW_PB400EEQX; PARTREV NA

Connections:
+3V3: R52.2; also elsewhere on the board
+12V: R32.1, R33.2; also elsewhere on the board
GND: C38.1, Q4.2 (S), Q5.2 (S), S2.2, S2.4; also elsewhere on the board
unnamed: Q4.3 (D), Q5.1 (G), R33.1
unnamed: C38.2, Q4.1 (G), R32.2
RST_: Q5.3 (D), R52.1, S2.1, S2.3; also elsewhere on the board

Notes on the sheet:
but it is recommended to hold RESET low for at least 250 ms after PVDD supply voltage is turned ON

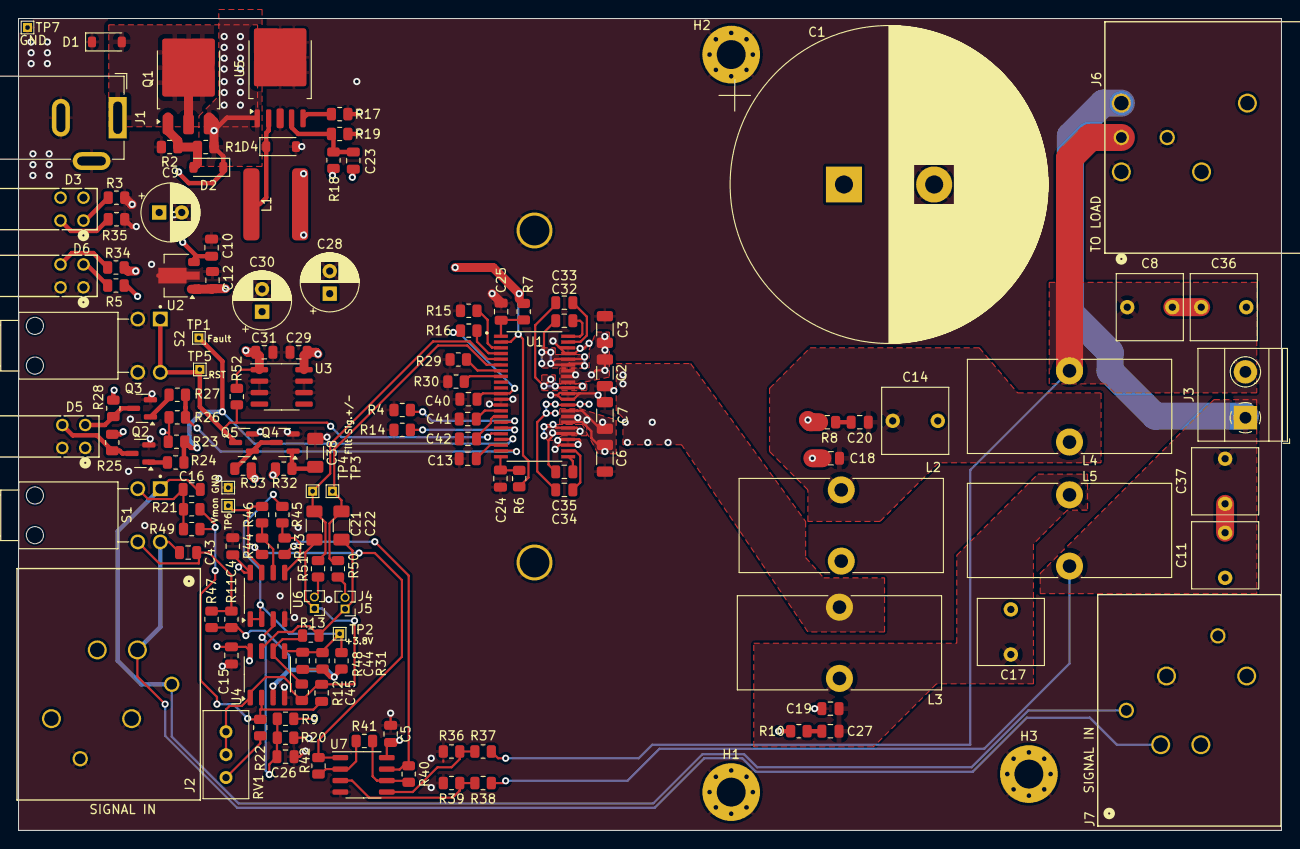
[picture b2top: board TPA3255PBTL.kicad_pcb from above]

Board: 4 copper layers, 140.0 x 90.0 mm, 140 parts (0 on the bottom side), 74 nets.

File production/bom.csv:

Designator,Footprint,Quantity,Value,LCSC Part #
C1,CP_Radial_D35.0mm_P10.00mm_SnapIn,1,4700u,
"C10, C12, C15, C24, C25, C26, C29, C31, C4, C5",0805,10,100n,
"C11, C14, C17, C36, C37, C8",C_Rect_L7.2mm_W7.2mm_P5.00mm_FKS2_FKP2_MKS2_MKP2,6,1u,
"C13, C40, C41",0805,3,1u,
"C16, C20, C27, C43",0805,4,10n,
"C18, C19",0805,2,1n,
"C2, C3, C6, C7",1206,4,1u,
"C21, C22, C38",1206,3,47u,
"C23, C32, C33, C34, C35",0805,5,33n,
"C28, C30, C9",CP_Radial_D6.3mm_P2.50mm,3,20u,
C42,0805,1,47n,
"C44, C45",0805,2,330p,
D1,D_SOD-123,1,D_TVS,
D2,D_SOD-123,1,6.3V,
"D3, D5, D6",IC4_WP934EB_2GD_KNB,3,LED_Dual_KAKA,
D4,D_SOD-123,1,D_Schottky,
J1,BarrelJack_GCT_DCJ200-10-A_Horizontal,1,Barrel_Jack_Switch,
"J2, J7",AC3FAH2-F-XLR,2,AC3FAH2-XLR,
J3,"TerminalBlock_Phoenix_MKDS-1,5-2-5.08_1x02_P5.08mm_Horizontal",1,Screw_Terminal_01x02,
"J4, J5",PinHeader_1x02_P1.27mm_Vertical,2,Conn_01x02_Pin,
J6,AC3MAH-AU-PRE_AMP,1,AC3MAH-AU-PRE,
L1,MWPY8040,1,100u,C501759
"L2, L3",L_Toroid_Vertical_L22.4mm_W10.2mm_P7.90mm_Vishay_TJ4,2,10u,
"L4, L5",L_Toroid_Vertical_L22.4mm_W10.2mm_P7.90mm_Vishay_TJ4,2,22u,
Q1,TO-252-3_TabPin4,1,DMP4015SK3,
"Q2, Q3, Q4, Q5",SOT-23,4,DMN10H220L,
"R1, R11, R12, R13, R2, R21, R3, R31, R37, R38, R40, R42, R43, R44, R45, R46, R47, R48, R49, R52, R9",0805,21,10k,
"R10, R8",0805,2,3R3,
"R14, R15, R16, R17, R4",0805,5,0,
"R18, R30",0805,2,30k,
"R19, R35, R5",0805,3,2.7k,
"R20, R22, R25, R28",0805,4,4.7k,
"R23, R26, R32, R33",0805,4,47k,
"R24, R27, R36, R39, R50, R51",0805,6,1k,
R29,0805,1,22k,
R34,0805,1,470,
"R6, R7",0805,2,3.3,
RV1,Potentiometer_Bourns_3296W_Vertical,1,500,
S1,SW_PB400EEQX,1,PB400EEQX,
S2,SW_PB400EEQX,1,PB400OAQX,
"TP1, TP2, TP3, TP4, TP5, TP6, TP7, TP8",TestPoint_THTPad_1.0x1.0mm_Drill0.5mm,8,TestPoint,
U1,SOP63P810X120-44N,1,TPA3255DDV,
U2,SOT-89-3,1,L78L12_SOT89,
U3,SOIC-8_3.9x4.9mm_P1.27mm,1,L78L33_SO8,
"U4, U6, U7",SO-8_3.9x4.9mm_P1.27mm,3,AD8512,
U5,XL7015E1,1,XL7015,

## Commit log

2022-08-26 First Draft
2022-08-26 Update Layout
2023-01-05 pre fab-no heatsink
2024-09-07 Update, Post mfg
2024-11-23 Pre mfg, Rev B
2024-11-23 add stp
2024-11-23 minor changes
2025-11-27 Add testing/ update README/ Current control
2025-11-27 Bug fix on THD
